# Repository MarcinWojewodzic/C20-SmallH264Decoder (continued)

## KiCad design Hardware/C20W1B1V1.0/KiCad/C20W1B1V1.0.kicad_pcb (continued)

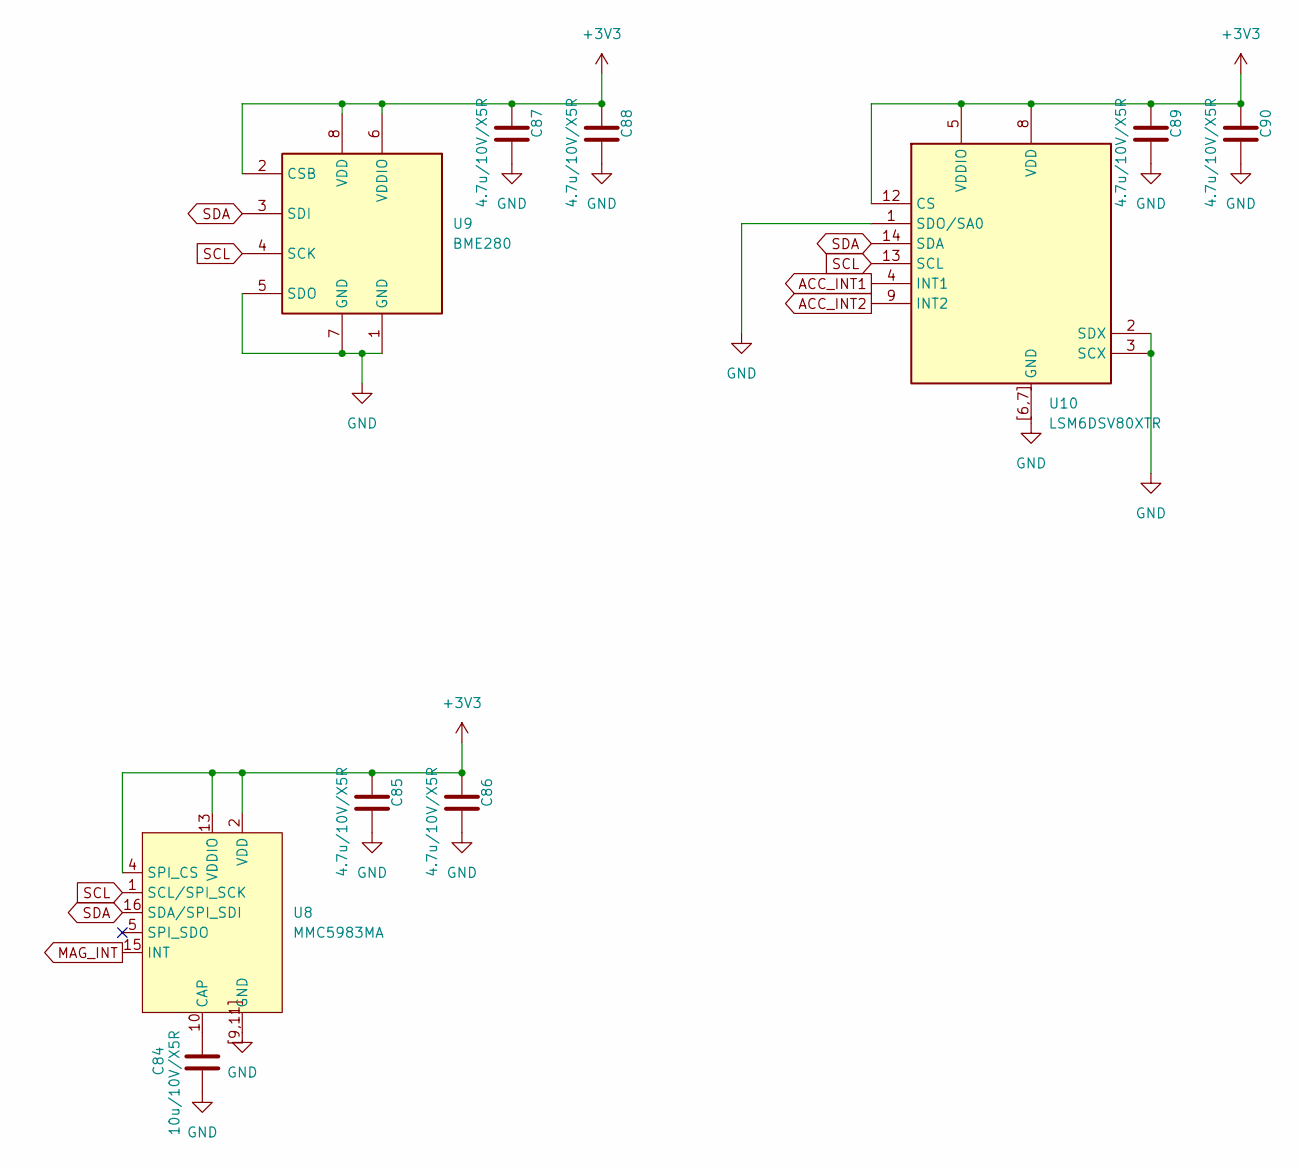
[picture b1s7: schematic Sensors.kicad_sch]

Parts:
C84: 10u/10V/X5R; C_0603_1608Metric
C85, C86, C87, C88, C89, C90: 4.7u/10V/X5R; C_0402_1005Metric
U8: MMC5983MA; LGA-16_3x3mm_P0.5mm
U9: BME280; Bosch_LGA-8_2.5x2.5mm_P0.65mm_ClockwisePinNumbering
U10: LSM6DSV80XTR; Bosch_LGA-14_3x2.5mm_P0.5mm; Manufacturer_Part_Number LSM6DSV80XTR

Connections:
+3V3: C85.1, C86.1, C87.1, C88.1, C89.1, C90.1, U8.2 (VDD), U8.4 (SPI_CS), U8.13 (VDDIO), U9.2 (CSB), U9.6 (VDDIO), U9.8 (VDD), U10.5 (VDDIO), U10.8 (VDD), U10.12 (CS); also elsewhere on the board
ACC_INT1: U10.4 (INT1)
ACC_INT2: U10.9 (INT2)
GND: C84.2, C85.2, C86.2, C87.2, C88.2, C89.2, C90.2, U8.9 (GND), U8.11 (GND), U8.[9,11] (GND), U9.1 (GND), U9.5 (SDO), U9.7 (GND), U10.1 (SDO/SA0), U10.2 (SDX), U10.3 (SCX), U10.6 (GND), U10.7 (GND), U10.[6,7] (GND); also elsewhere on the board
MAG_INT: U8.15 (INT)
unnamed: C84.1, U8.10 (CAP)
SCL: U8.1 (SCL/SPI_SCK), U9.4 (SCK), U10.13 (SCL); also elsewhere on the board
SDA: U8.16 (SDA/SPI_SDI), U9.3 (SDI), U10.14 (SDA); also elsewhere on the board

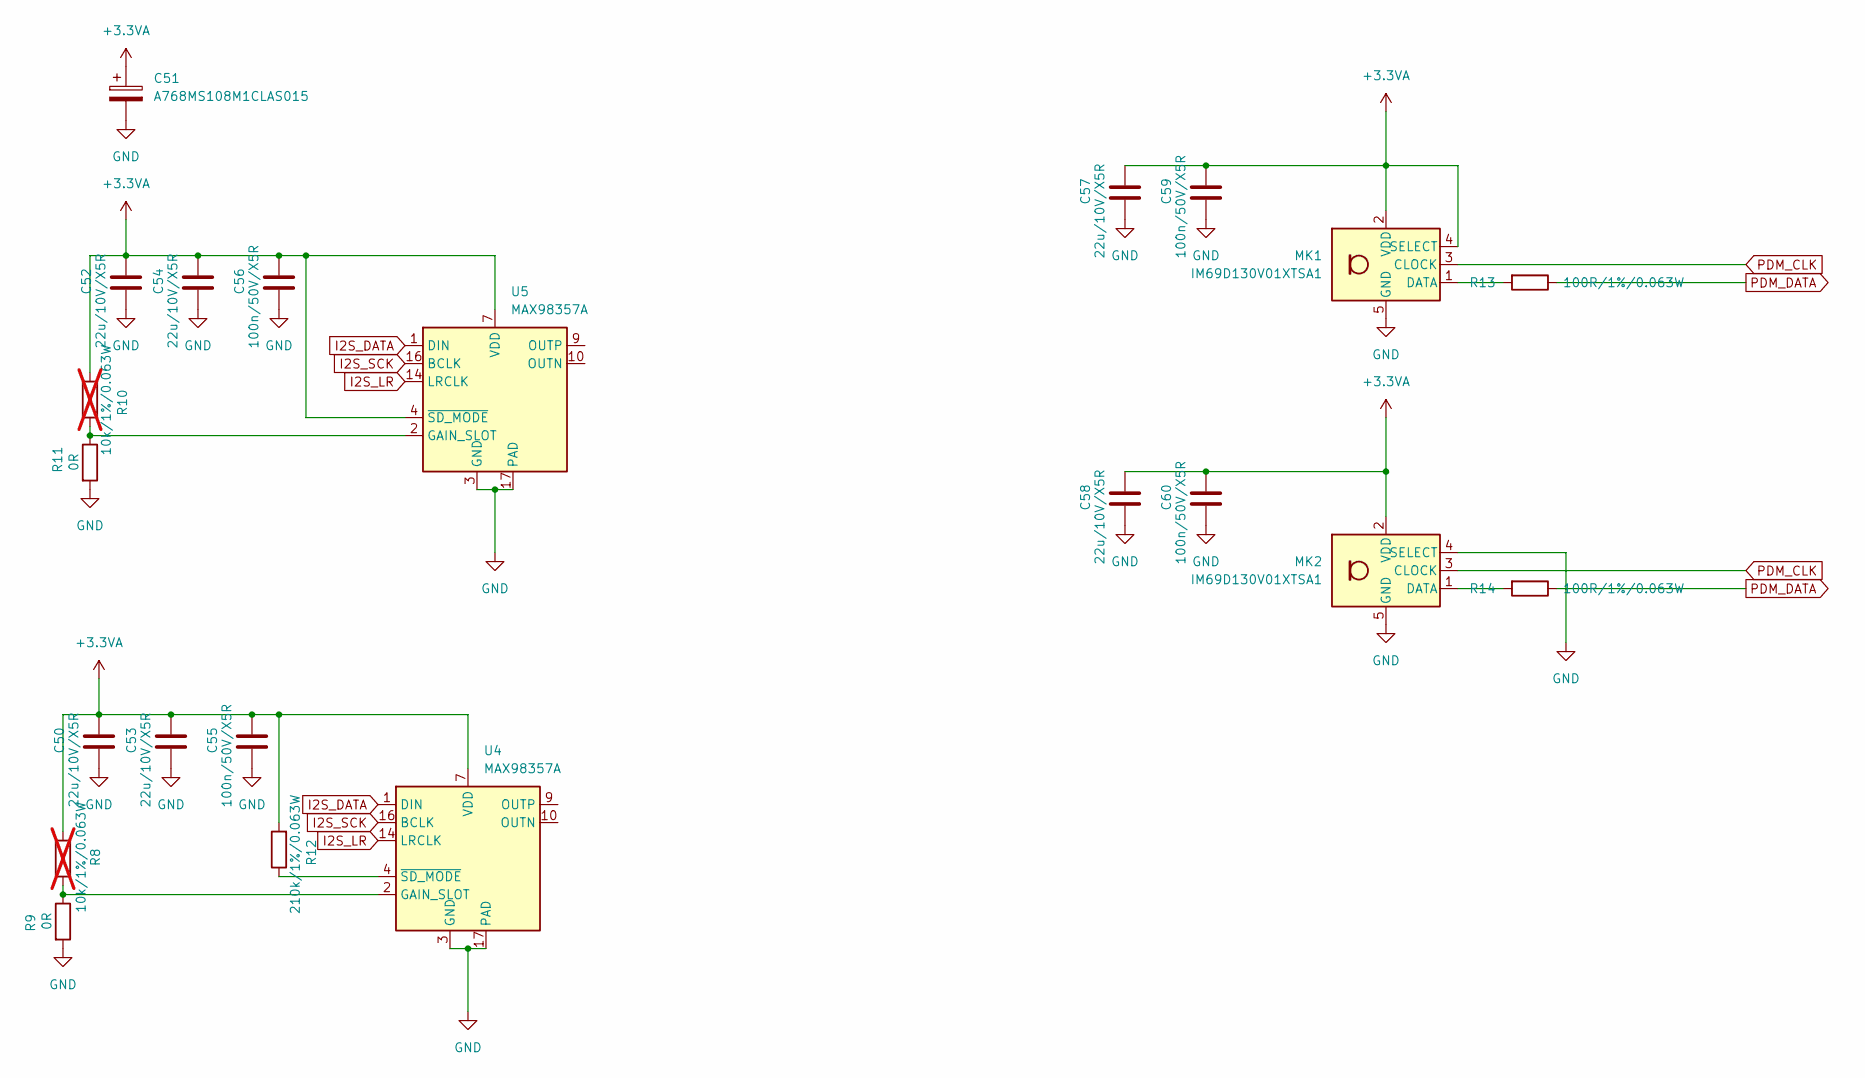
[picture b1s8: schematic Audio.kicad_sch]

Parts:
C50, C52, C53, C54, C57, C58: 22u/10V/X5R; C_0603_1608Metric
C51: A768MS108M1CLAS015; CP_Elec_10x12.6
C55, C56, C59, C60: 100n/50V/X5R; C_0402_1005Metric
MK1, MK2: IM69D130V01XTSA1; Infineon_PG-LLGA-5-1
R8, R10: 10k/1%/0.063W; R_0402_1005Metric; not fitted
R9, R11: 0R; R_0402_1005Metric
R12: 210k/1%/0.063W; R_0402_1005Metric
R13, R14: 100R/1%/0.063W; R_0402_1005Metric
U4, U5: MAX98357A; TQFN-16-1EP_3x3mm_P0.5mm_EP1.23x1.23mm

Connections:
+3.3VA: C50.1, C51.1, C52.1, C53.1, C54.1, C55.1, C56.1, C57.1, C58.1, C59.1, C60.1, MK1.2 (VDD), MK1.4 (SELECT), MK2.2 (VDD), R8.2, R10.2, R12.2, U4.7 (VDD), U4.8 (VDD), U5.4 (~SD_MODE), U5.7 (VDD), U5.8 (VDD); also elsewhere on the board
GND: C50.2, C51.2, C52.2, C53.2, C54.2, C55.2, C56.2, C57.2, C58.2, C59.2, C60.2, MK1.5 (GND), MK2.4 (SELECT), MK2.5 (GND), R9.2, R11.2, U4.3 (GND), U4.11 (GND), U4.15 (GND), U4.17 (PAD), U5.3 (GND), U5.11 (GND), U5.15 (GND), U5.17 (PAD); also elsewhere on the board
I2S_DATA: U4.1 (DIN), U5.1 (DIN); also elsewhere on the board
I2S_LR: U4.14 (LRCLK), U5.14 (LRCLK); also elsewhere on the board
I2S_SCK: U4.16 (BCLK), U5.16 (BCLK); also elsewhere on the board
unnamed: MK1.1 (DATA), R13.2
unnamed: MK2.1 (DATA), R14.2
unnamed: R8.1, R9.1, U4.2 (GAIN_SLOT)
unnamed: R12.1, U4.4 (~SD_MODE)
unnamed: R10.1, R11.1, U5.2 (GAIN_SLOT)
PDM_CLK: MK1.3 (CLOCK), MK2.3 (CLOCK); also elsewhere on the board
PDM_DATA: R13.1, R14.1; also elsewhere on the board

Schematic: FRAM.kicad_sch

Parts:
C91: 4.7u/10V/X5R; C_0402_1005Metric
U11: FM24CL04B-GTR; SOIC-8_3.9x4.9mm_P1.27mm

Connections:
+3V3: C91.1, U11.8 (VDD); also elsewhere on the board
GND: C91.2, U11.2 (A1), U11.3 (A2), U11.4 (GND), U11.7 (WP); also elsewhere on the board
SCL: U11.6 (SCL); also elsewhere on the board
SDA: U11.5 (SDA); also elsewhere on the board

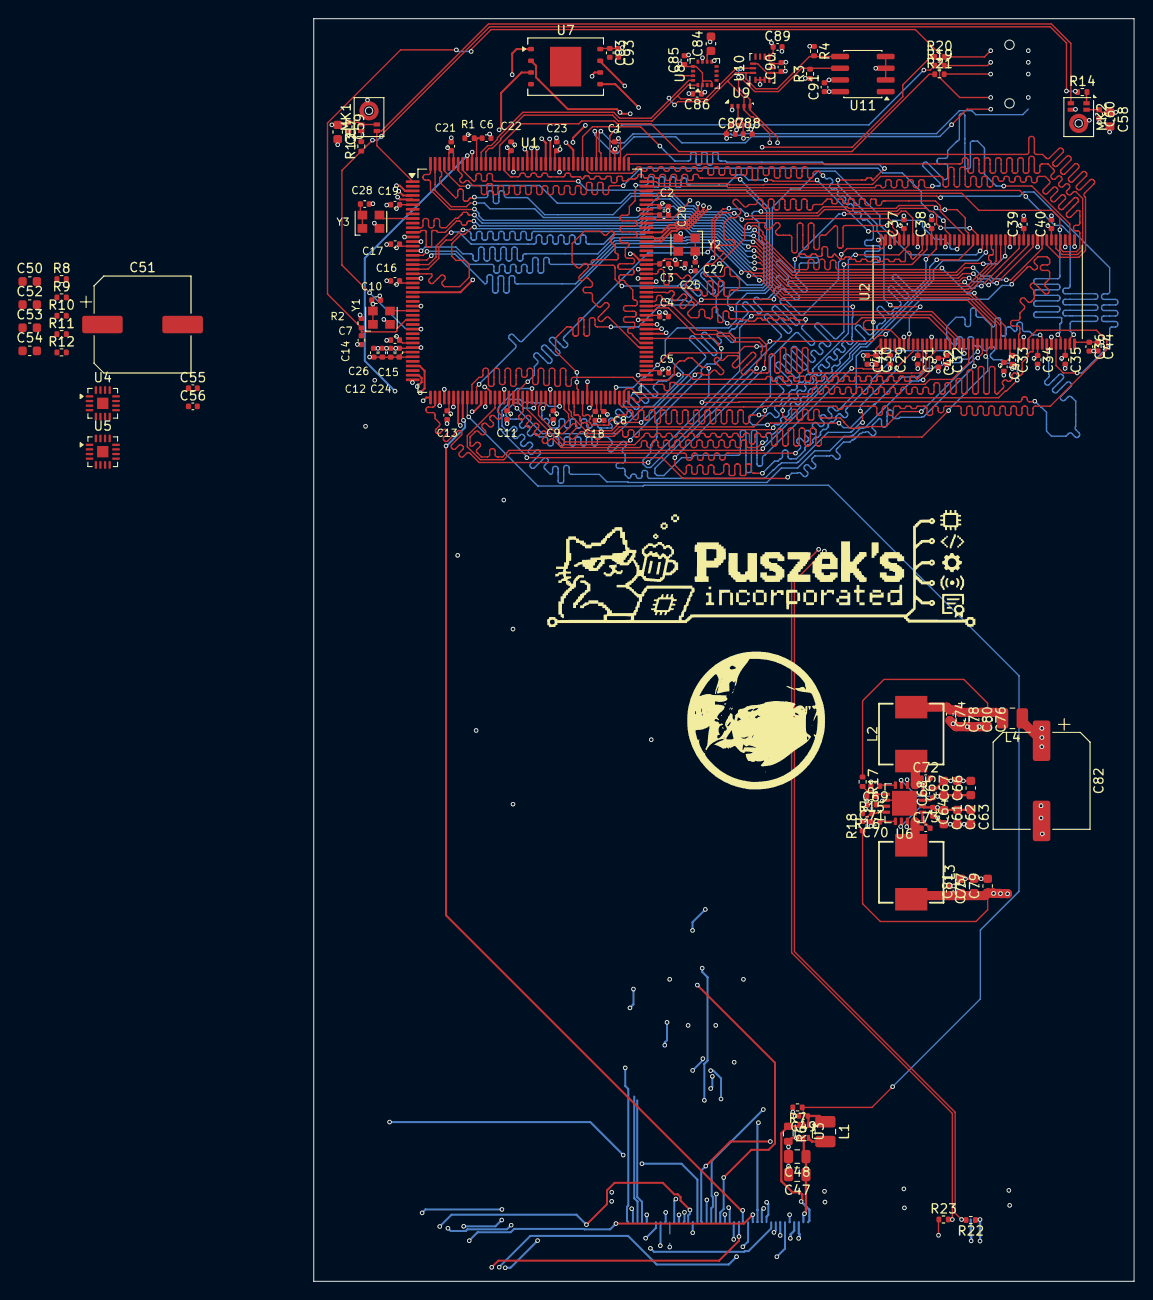
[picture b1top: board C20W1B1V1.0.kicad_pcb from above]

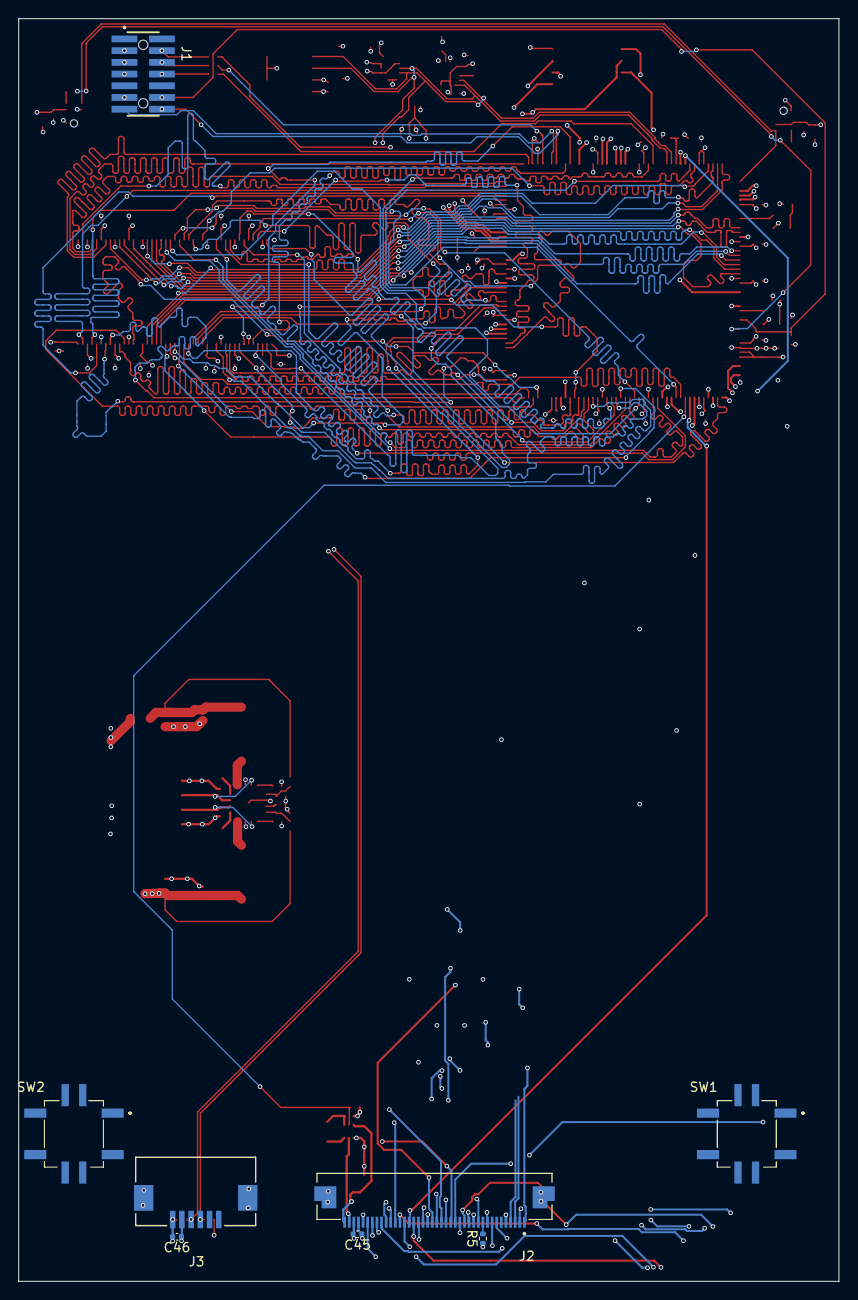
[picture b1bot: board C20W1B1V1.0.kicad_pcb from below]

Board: 6 copper layers, 89.0 x 137.0 mm, 140 parts (8 on the bottom side), 140 nets.

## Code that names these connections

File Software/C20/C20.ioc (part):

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Mcu.Name=STM32H753IITx
Mcu.Package=LQFP176
Mcu.UserName=STM32H753IITx
PA1.GPIOParameters=GPIO_Speed
PA1.GPIO_Speed=GPIO_SPEED_FREQ_VERY_HIGH
PA1.Mode=RGB888
PA1.Signal=LTDC_R2
PA10.GPIOParameters=GPIO_Speed
PA10.GPIO_Speed=GPIO_SPEED_FREQ_VERY_HIGH
PA10.Mode=RGB888
PA10.Signal=LTDC_B1
PA11.GPIOParameters=GPIO_Speed
PA11.GPIO_Speed=GPIO_SPEED_FREQ_VERY_HIGH
PA11.Mode=Host_Only
PA11.Signal=USB_OTG_FS_DM
PA12.GPIOParameters=GPIO_Speed
PA12.GPIO_Speed=GPIO_SPEED_FREQ_VERY_HIGH
PA12.Mode=Host_Only
PA12.Signal=USB_OTG_FS_DP
PA13\ (JTMS/SWDIO).Mode=Trace_Asynchronous_SW
PA13\ (JTMS/SWDIO).Signal=DEBUG_JTMS-SWDIO
PA14\ (JTCK/SWCLK).Mode=Trace_Asynchronous_SW
PA14\ (JTCK/SWCLK).Signal=DEBUG_JTCK-SWCLK
PA3.GPIOParameters=GPIO_Speed
PA3.GPIO_Speed=GPIO_SPEED_FREQ_VERY_HIGH
PA3.Mode=RGB888
PA3.Signal=LTDC_B5
PA4.GPIOParameters=GPIO_Speed
PA4.GPIO_Speed=GPIO_SPEED_FREQ_VERY_HIGH
PA4.Mode=RGB888
PA4.Signal=LTDC_VSYNC
PA5.GPIOParameters=GPIO_Speed
PA5.GPIO_Speed=GPIO_SPEED_FREQ_VERY_HIGH
PA5.Mode=RGB888
PA5.Signal=LTDC_R4
PA6.GPIOParameters=GPIO_Speed
PA6.GPIO_Speed=GPIO_SPEED_FREQ_VERY_HIGH
PA6.Mode=RGB888
PA6.Signal=LTDC_G2
PA7.GPIOParameters=GPIO_Speed
PA7.GPIO_Speed=GPIO_SPEED_FREQ_VERY_HIGH
PA7.Signal=S_TIM3_CH2
PA8.GPIOParameters=GPIO_Speed
PA8.GPIO_Speed=GPIO_SPEED_FREQ_VERY_HIGH
PA8.Mode=RGB888
PA8.Signal=LTDC_B3
PA9.GPIOParameters=GPIO_Speed
PA9.GPIO_Speed=GPIO_SPEED_FREQ_VERY_HIGH
PA9.Mode=RGB888
PA9.Signal=LTDC_R5
PB0.GPIOParameters=GPIO_Speed
PB0.GPIO_Speed=GPIO_SPEED_FREQ_VERY_HIGH
PB0.Mode=RGB888
PB0.Signal=LTDC_R3
PB1.GPIOParameters=GPIO_Speed
PB1.GPIO_Speed=GPIO_SPEED_FREQ_VERY_HIGH
PB1.Mode=RGB888
PB1.Signal=LTDC_R6
PB10.GPIOParameters=GPIO_Speed
PB10.GPIO_Speed=GPIO_SPEED_FREQ_VERY_HIGH
PB10.Mode=Single Bank 1
PB10.Signal=QUADSPI_BK1_NCS
PB11.GPIOParameters=GPIO_Speed
PB11.GPIO_Speed=GPIO_SPEED_FREQ_VERY_HIGH
PB11.Mode=RGB888
PB11.Signal=LTDC_G5
PB2.GPIOParameters=GPIO_Speed
PB2.GPIO_Speed=GPIO_SPEED_FREQ_VERY_HIGH
PB2.Mode=Single Bank 1
PB2.Signal=QUADSPI_CLK
PB3\ (JTDO/TRACESWO).Mode=Trace_Asynchronous_SW
PB3\ (JTDO/TRACESWO).Signal=DEBUG_JTDO-SWO
PB6.GPIOParameters=GPIO_Speed
PB6.GPIO_Speed=GPIO_SPEED_FREQ_VERY_HIGH
PB6.Mode=I2C
PB6.Signal=I2C1_SCL
PB7.GPIOParameters=GPIO_Speed
PB7.GPIO_Speed=GPIO_SPEED_FREQ_VERY_HIGH
PB7.Mode=I2C
PB7.Signal=I2C1_SDA
PB8.GPIOParameters=GPIO_Speed
PB8.GPIO_Speed=GPIO_SPEED_FREQ_VERY_HIGH
PB8.Mode=RGB888
PB8.Signal=LTDC_B6
PB9.GPIOParameters=GPIO_Speed
PB9.GPIO_Speed=GPIO_SPEED_FREQ_VERY_HIGH
PB9.Mode=RGB888
PB9.Signal=LTDC_B7
PC1.GPIOParameters=GPIO_Speed
PC1.GPIO_Speed=GPIO_SPEED_FREQ_VERY_HIGH
PC1.Mode=PDM_Master_Mode_CK1
PC1.Signal=SAI1_D1
PC10.Mode=Asynchronous
PC10.Signal=UART4_TX
PC11.Mode=Asynchronous
PC11.Signal=UART4_RX
PC12.Mode=SD_1_bit
PC12.Signal=SDMMC1_CK
PC14-OSC32_IN\ (OSC32_IN).Mode=LSE-External-Clock-Source
PC14-OSC32_IN\ (OSC32_IN).Signal=RCC_OSC32_IN
PC4.Mode=SdramChipSelect1_1
PC4.Signal=FMC_SDNE0
PC5.Mode=SdramChipSelect1_1
PC5.Signal=FMC_SDCKE0
PC6.GPIOParameters=GPIO_Speed
PC6.GPIO_Speed=GPIO_SPEED_FREQ_VERY_HIGH
PC6.Mode=RGB888
PC6.Signal=LTDC_HSYNC
PC8.Mode=SD_1_bit
PC8.Signal=SDMMC1_D0
PC9.GPIOParameters=GPIO_Speed
PC9.GPIO_Speed=GPIO_SPEED_FREQ_VERY_HIGH
PC9.Mode=Audio_ClockIn
PC9.Signal=I2S_CKIN
PD0.Signal=FMC_D2_DA2
PD1.Signal=FMC_D3_DA3
PD10.Signal=FMC_D15_DA15
PD11.GPIOParameters=GPIO_Speed
PD11.GPIO_Speed=GPIO_SPEED_FREQ_VERY_HIGH
PD11.Mode=Single Bank 1
PD11.Signal=QUADSPI_BK1_IO0
PD12.GPIOParameters=GPIO_Speed
PD12.GPIO_Speed=GPIO_SPEED_FREQ_VERY_HIGH
PD12.Mode=Single Bank 1
PD12.Signal=QUADSPI_BK1_IO1
PD13.GPIOParameters=GPIO_Speed
PD13.GPIO_Speed=GPIO_SPEED_FREQ_VERY_HIGH
PD13.Mode=Single Bank 1
PD13.Signal=QUADSPI_BK1_IO3
PD14.Signal=FMC_D0_DA0
PD15.Signal=FMC_D1_DA1
PD2.Mode=SD_1_bit
PD2.Signal=SDMMC1_CMD
PD3.GPIOParameters=GPIO_Speed
PD3.GPIO_Speed=GPIO_SPEED_FREQ_VERY_HIGH
PD3.Mode=RGB888
PD3.Signal=LTDC_G7
PD6.GPIOParameters=GPIO_Speed
PD6.GPIO_Speed=GPIO_SPEED_FREQ_VERY_HIGH
PD6.Mode=RGB888
PD6.Signal=LTDC_B2
PD7.GPIOParameters=GPIO_Speed
PD7.GPIO_Speed=GPIO_SPEED_FREQ_VERY_HIGH
PD7.Mode=Full_Duplex_Master
PD7.Signal=SPI1_MOSI
PD8.Signal=FMC_D13_DA13
PD9.Signal=FMC_D14_DA14
PE0.Signal=FMC_NBL0
PE1.Signal=FMC_NBL1
PE10.Signal=FMC_D7_DA7
PE11.Signal=FMC_D8_DA8
PE12.Signal=FMC_D9_DA9
PE13.Signal=FMC_D10_DA10
PE14.Signal=FMC_D11_DA11
PE15.Signal=FMC_D12_DA12
PE2.GPIOParameters=GPIO_Speed
PE2.GPIO_Speed=GPIO_SPEED_FREQ_VERY_HIGH
PE2.Mode=PDM_Master_Mode_CK1
PE2.Signal=SAI1_CK1
PE4.GPIOParameters=GPIO_Speed
PE4.GPIO_Speed=GPIO_SPEED_FREQ_VERY_HIGH
PE4.Mode=RGB888
PE4.Signal=LTDC_B0
PE5.GPIOParameters=GPIO_Speed
PE5.GPIO_Speed=GPIO_SPEED_FREQ_VERY_HIGH
PE5.Mode=RGB888
PE5.Signal=LTDC_G0
PE6.GPIOParameters=GPIO_Speed
PE6.GPIO_Speed=GPIO_SPEED_FREQ_VERY_HIGH
PE6.Mode=RGB888
PE6.Signal=LTDC_G1
PE7.Signal=FMC_D4_DA4
PE8.Signal=FMC_D5_DA5
PE9.Signal=FMC_D6_DA6
PF0.Signal=FMC_A0
PF1.Signal=FMC_A1
PF10.GPIOParameters=GPIO_Speed
PF10.GPIO_Speed=GPIO_SPEED_FREQ_VERY_HIGH
PF10.Mode=RGB888
PF10.Signal=LTDC_DE
PF11.Signal=FMC_SDNRAS
PF12.Signal=FMC_A6
PF13.Signal=FMC_A7
PF14.Signal=FMC_A8
PF15.Signal=FMC_A9
PF2.Signal=FMC_A2
PF3.Signal=FMC_A3
PF4.Signal=FMC_A4
PF5.Signal=FMC_A5
PF6.GPIOParameters=GPIO_Speed
PF6.GPIO_Speed=GPIO_SPEED_FREQ_VERY_HIGH
PF6.Mode=SAI_B_Master
PF6.Signal=SAI1_SD_B
PF7.GPIOParameters=GPIO_Speed
PF7.GPIO_Speed=GPIO_SPEED_FREQ_VERY_HIGH
PF7.Mode=Single Bank 1
PF7.Signal=QUADSPI_BK1_IO2
PF8.GPIOParameters=GPIO_Speed
PF8.GPIO_Speed=GPIO_SPEED_FREQ_VERY_HIGH
PF8.Mode=SAI_B_Master
PF8.Signal=SAI1_SCK_B
PF9.GPIOParameters=GPIO_Speed
PF9.GPIO_Speed=GPIO_SPEED_FREQ_VERY_HIGH
PF9.Mode=SAI_B_Master
PF9.Signal=SAI1_FS_B
PG0.Signal=FMC_A10
PG1.Signal=FMC_A11
PG10.GPIOParameters=GPIO_Speed
PG10.GPIO_Speed=GPIO_SPEED_FREQ_VERY_HIGH
PG10.Mode=RGB888
PG10.Signal=LTDC_G3
PG11.GPIOParameters=GPIO_Speed
PG11.GPIO_Speed=GPIO_SPEED_FREQ_VERY_HIGH
PG11.Mode=Full_Duplex_Master
PG11.Signal=SPI1_SCK
PG12.GPIOParameters=GPIO_Speed
PG12.GPIO_Speed=GPIO_SPEED_FREQ_VERY_HIGH
PG12.Mode=RGB888
PG12.Signal=LTDC_B4
PG15.Signal=FMC_SDNCAS
PG2.Signal=FMC_A12
PG4.Signal=FMC_A14_BA0
PG5.Signal=FMC_A15_BA1
PG6.GPIOParameters=GPIO_Speed
PG6.GPIO_Speed=GPIO_SPEED_FREQ_VERY_HIGH
PG6.Mode=RGB888
PG6.Signal=LTDC_R7
PG7.GPIOParameters=GPIO_Speed
PG7.GPIO_Speed=GPIO_SPEED_FREQ_VERY_HIGH
PG7.Mode=RGB888
PG7.Signal=LTDC_CLK
PG8.Signal=FMC_SDCLK
PG9.GPIOParameters=GPIO_Speed
PG9.GPIO_Speed=GPIO_SPEED_FREQ_VERY_HIGH
PG9.Mode=Full_Duplex_Master
PG9.Signal=SPI1_MISO
PH0-OSC_IN\ (PH0).Mode=HSE-External-Clock-Source
PH0-OSC_IN\ (PH0).Signal=RCC_OSC_IN
PH10.Signal=FMC_D18
PH11.Signal=FMC_D19
PH12.Signal=FMC_D20
PH13.Signal=FMC_D21
PH14.Signal=FMC_D22
PH15.Signal=FMC_D23
PH2.GPIOParameters=GPIO_Speed
PH2.GPIO_Speed=GPIO_SPEED_FREQ_VERY_HIGH
PH2.Mode=RGB888
PH2.Signal=LTDC_R0
PH3.GPIOParameters=GPIO_Speed
PH3.GPIO_Speed=GPIO_SPEED_FREQ_VERY_HIGH
PH3.Mode=RGB888
PH3.Signal=LTDC_R1
PH4.GPIOParameters=GPIO_Speed
PH4.GPIO_Speed=GPIO_SPEED_FREQ_VERY_HIGH
PH4.Mode=RGB888
PH4.Signal=LTDC_G4
PH5.Signal=FMC_SDNWE
PH8.Signal=FMC_D16
PH9.Signal=FMC_D17
PI0.Signal=FMC_D24
PI1.Signal=FMC_D25
PI10.Signal=FMC_D31
PI11.GPIOParameters=GPIO_Speed
PI11.GPIO_Speed=GPIO_SPEED_FREQ_VERY_HIGH
PI11.Mode=RGB888
PI11.Signal=LTDC_G6
PI2.Signal=FMC_D26
PI3.Signal=FMC_D27
PI4.Signal=FMC_NBL2
PI5.Signal=FMC_NBL3
PI6.Signal=FMC_D28
PI7.Signal=FMC_D29
PI9.Signal=FMC_D30
RCC.SYSCLKFreq_VALUE=480000000
RCC.SYSCLKSource=RCC_SYSCLKSOURCE_PLLCLK
board=custom

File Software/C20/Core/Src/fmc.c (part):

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  __HAL_RCC_FMC_CLK_ENABLE();

  /** FMC GPIO Configuration
  PI9   ------> FMC_D30
  PI10   ------> FMC_D31
  PF0   ------> FMC_A0
  PF1   ------> FMC_A1
  PF2   ------> FMC_A2
  PF3   ------> FMC_A3
  PF4   ------> FMC_A4
  PF5   ------> FMC_A5
  PH5   ------> FMC_SDNWE
  PC4   ------> FMC_SDNE0
  PC5   ------> FMC_SDCKE0
  PF11   ------> FMC_SDNRAS
  PF12   ------> FMC_A6
  PF13   ------> FMC_A7
  PF14   ------> FMC_A8
  PF15   ------> FMC_A9
  PG0   ------> FMC_A10
  PG1   ------> FMC_A11
  PE7   ------> FMC_D4
  PE8   ------> FMC_D5
  PE9   ------> FMC_D6
  PE10   ------> FMC_D7
  PE11   ------> FMC_D8
  PE12   ------> FMC_D9
  PE13   ------> FMC_D10
  PE14   ------> FMC_D11
  PE15   ------> FMC_D12
  PH8   ------> FMC_D16
  PH9   ------> FMC_D17
  PH10   ------> FMC_D18
  PH11   ------> FMC_D19
  PH12   ------> FMC_D20
  PD8   ------> FMC_D13
  PD9   ------> FMC_D14
  PD10   ------> FMC_D15
  PD14   ------> FMC_D0
  PD15   ------> FMC_D1
  PG2   ------> FMC_A12
  PG4   ------> FMC_BA0
  PG5   ------> FMC_BA1
  PG8   ------> FMC_SDCLK
  PH13   ------> FMC_D21
  PH14   ------> FMC_D22
  PH15   ------> FMC_D23
  PI0   ------> FMC_D24
  PI1   ------> FMC_D25
  PI2   ------> FMC_D26
  PI3   ------> FMC_D27
  PD0   ------> FMC_D2
  PD1   ------> FMC_D3
  PG15   ------> FMC_SDNCAS
  PE0   ------> FMC_NBL0
  PE1   ------> FMC_NBL1
  PI4   ------> FMC_NBL2
  PI5   ------> FMC_NBL3
  PI6   ------> FMC_D28
  PI7   ------> FMC_D29
  */
  /* GPIO_InitStruct */
  GPIO_InitStruct.Pin = GPIO_PIN_9|GPIO_PIN_10|GPIO_PIN_0|GPIO_PIN_1
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  __HAL_RCC_FMC_CLK_DISABLE();

  /** FMC GPIO Configuration
  PI9   ------> FMC_D30
  PI10   ------> FMC_D31
  PF0   ------> FMC_A0
  PF1   ------> FMC_A1
  PF2   ------> FMC_A2
  PF3   ------> FMC_A3
  PF4   ------> FMC_A4
  PF5   ------> FMC_A5
  PH5   ------> FMC_SDNWE
  PC4   ------> FMC_SDNE0
  PC5   ------> FMC_SDCKE0
  PF11   ------> FMC_SDNRAS
  PF12   ------> FMC_A6
  PF13   ------> FMC_A7
  PF14   ------> FMC_A8
  PF15   ------> FMC_A9
  PG0   ------> FMC_A10
  PG1   ------> FMC_A11
  PE7   ------> FMC_D4
  PE8   ------> FMC_D5
  PE9   ------> FMC_D6
  PE10   ------> FMC_D7
  PE11   ------> FMC_D8
  PE12   ------> FMC_D9
  PE13   ------> FMC_D10
  PE14   ------> FMC_D11
  PE15   ------> FMC_D12
  PH8   ------> FMC_D16
  PH9   ------> FMC_D17
  PH10   ------> FMC_D18
  PH11   ------> FMC_D19
  PH12   ------> FMC_D20
  PD8   ------> FMC_D13
  PD9   ------> FMC_D14
  PD10   ------> FMC_D15
  PD14   ------> FMC_D0
  PD15   ------> FMC_D1
  PG2   ------> FMC_A12
  PG4   ------> FMC_BA0
  PG5   ------> FMC_BA1
  PG8   ------> FMC_SDCLK
  PH13   ------> FMC_D21
  PH14   ------> FMC_D22
  PH15   ------> FMC_D23
  PI0   ------> FMC_D24
  PI1   ------> FMC_D25
  PI2   ------> FMC_D26
  PI3   ------> FMC_D27
  PD0   ------> FMC_D2
  PD1   ------> FMC_D3
  PG15   ------> FMC_SDNCAS
  PE0   ------> FMC_NBL0
  PE1   ------> FMC_NBL1
  PI4   ------> FMC_NBL2
  PI5   ------> FMC_NBL3
  PI6   ------> FMC_D28
  PI7   ------> FMC_D29
  */

  HAL_GPIO_DeInit(GPIOI, GPIO_PIN_9|GPIO_PIN_10|GPIO_PIN_0|GPIO_PIN_1
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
